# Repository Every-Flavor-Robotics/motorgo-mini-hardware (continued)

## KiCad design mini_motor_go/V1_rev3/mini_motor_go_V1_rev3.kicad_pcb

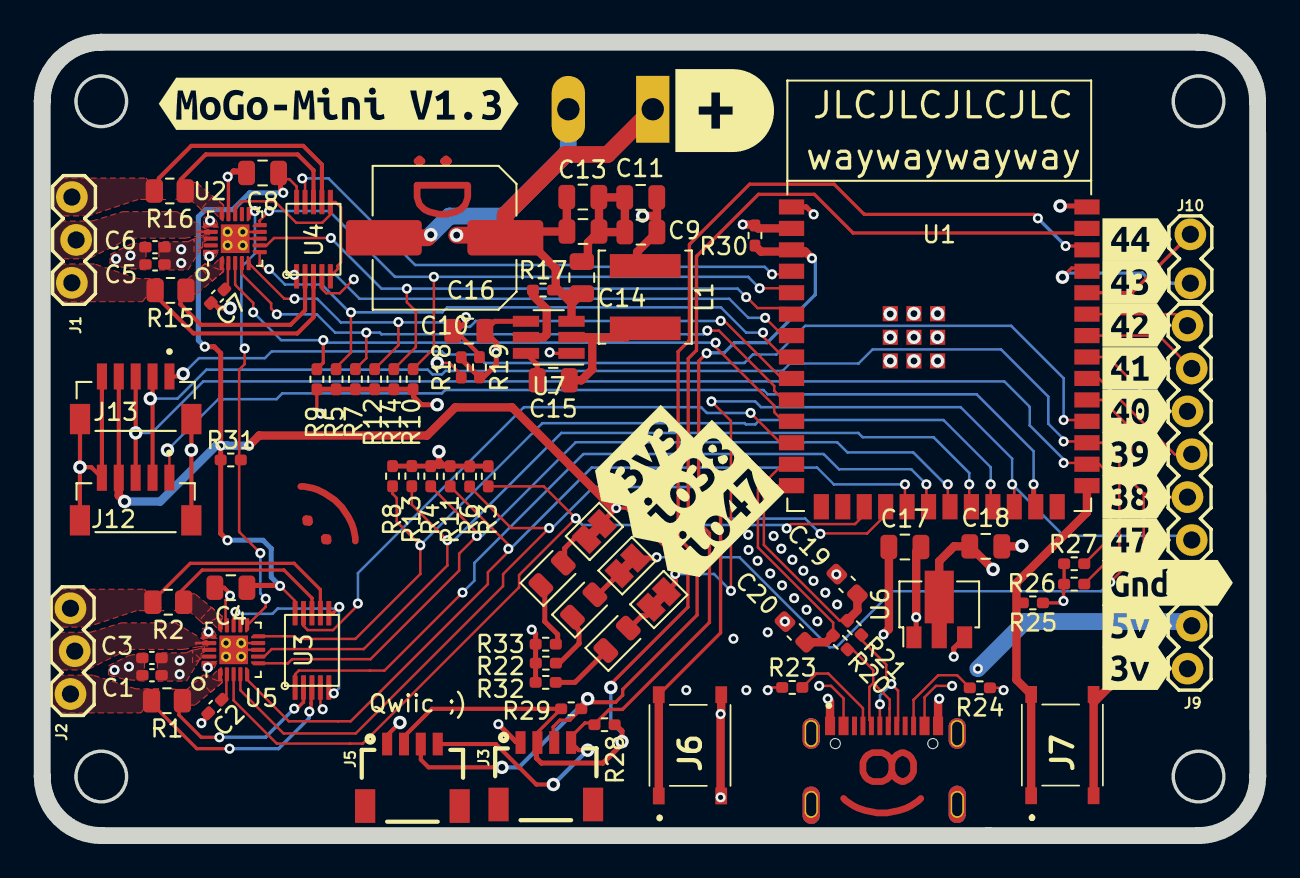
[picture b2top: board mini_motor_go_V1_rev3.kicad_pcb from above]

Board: 4 copper layers, 72.0 x 47.0 mm, 95 parts (0 on the bottom side), 68 nets.

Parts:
C1, C2, C3, C5, C6, C7: 10NF; C_0402_1005Metric_Pad0.74x0.62mm_HandSolder
C4, C8: 0.1UF; C_0805_2012Metric
C9, C11, C18: 22uF; C_0805_2012Metric
C10: 220uF; C_Elec_8x10.2
C12, C13, C17: 10uF; C_0805_2012Metric
C14, C15, C16: .1uF; C_0805_2012Metric
C19, C20: DNP; C_0603_1608Metric_Pad1.08x0.95mm_HandSolder
D1, D2, D3: LED; LED_0805_2012Metric
J1, J2: CONN_03POLAR_LOCK; 1X03_LOCK
J3, J5: I2C_STANDARDQWIIC; 1X04_1MM_RA
J6, J7: PTS526SM08SMTR2LFS
J8: TerminalBlock_Altech_AK300-2_P5.00mm
J9: Conn_01x09_Pin; 1X09_LOCK
J10: Conn_01x02_Pin; 1X02_LOCK
J11: USB4520-03-0-A_REVA; GCT_USB4520-03-0-A_REVA
J12, J13: BM05B-SRSS-TB_LF__SN_; JST_BM05B-SRSS-TB_LF__SN_
JP1, JP2, JP3: SolderJumper_2_Bridged; SolderJumper-2_P1.3mm_Bridged_Pad1.0x1.5mm
L1: SRP3212A-4R7M; L_Changjiang_FNR5020S
R1, R2, R15, R16: R_Shunt_US; R_0805_2012Metric
R3, R4, R5, R6, R7, R8, R9, R10, R11, R12, R13, R14: 1K; R_0402_1005Metric_Pad0.72x0.64mm_HandSolder
R17, R19: 54.9k; R_0402_1005Metric_Pad0.72x0.64mm_HandSolder
R18: 10k; R_0402_1005Metric_Pad0.72x0.64mm_HandSolder
R20, R21: 0; R_0402_1005Metric_Pad0.72x0.64mm_HandSolder
R22, R32, R33: 1k; R_0402_1005Metric_Pad0.72x0.64mm_HandSolder
R23, R24, R25, R26, R27, R28, R29, R30, R31: 5k1; R_0402_1005Metric_Pad0.72x0.64mm_HandSolder
U1: ESP32-S3-WROOM-1
U2, U5: TMC6300; TMC6300 3x3mm
U3, U4: INA2181; INA2181_VSSOP_10
U6: AZ1117C; SOT-89-3
U7: TPS562208; SOT-23-6_Handsoldering
kibuzzard-65733A0D: G***; kibuzzard-65733A0D
kibuzzard-65733A1B: G***; kibuzzard-65733A1B
kibuzzard-65733C02: G***; kibuzzard-65733C02
kibuzzard-65733C2B: G***; kibuzzard-65733C2B
kibuzzard-65733C3A: G***; kibuzzard-65733C3A
kibuzzard-65733C12: G***; kibuzzard-65733C12
kibuzzard-65733C20: G***; kibuzzard-65733C20
kibuzzard-65733C45: G***; kibuzzard-65733C45
kibuzzard-65733C60: G***; kibuzzard-65733C60
kibuzzard-65733C66: G***; kibuzzard-65733C66
kibuzzard-65733C85: G***; kibuzzard-65733C85
kibuzzard-65733FCF: G***; kibuzzard-65733FCF
kibuzzard-65733FF1: G***; kibuzzard-65733FF1
kibuzzard-66038D2F: G***; kibuzzard-66038D2F
kibuzzard-6573395A: G***; kibuzzard-6573395A
kibuzzard-65733965: G***; kibuzzard-65733965

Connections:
+3.3V: C4.1, C8.1, C18.1, J3.2 (VCC), J5.2 (VCC), J9.1, J12.4, J13.4, JP3.2 (B), R25.1, R26.1, R27.1, R28.1, R29.1, R30.1, R31.1, U1.2 (3V3), U3.10 (VS), U4.10 (VS), U6.2 (out)
+5V: C9.1, C11.1, C16.1, C17.1, J9.2, J11.A4_B9 (VBUS_A), J11.B4_A9 (VBUS_B), L1.1, R19.1, U6.3 (in)
+BATT: C1.1, C2.2, C3.2, C5.1, C6.2, C7.2, C10.1 (+), C12.2, C13.2, C14.2, J8.1 (+), R17.2, U2.18 (VS), U5.18 (VS), U7.3 (Vin)
/motor_controls/standby: R31.2, U2.11 (VIO/STDBY), U5.11 (VIO/STDBY)
GND: C1.2, C3.1, C4.2, C5.2, C6.1, C8.2, C10.2 (-), C17.2, C18.2, C19.2, C20.2, J3.1 (GND), J5.1 (GND), J6.3, J6.4, J7.3, J7.4, J8.2 (-), J9.3, J11.A1_B12 (GND_A), J11.B1_A12 (GND_B), J12.5, J12.S1 (SHIELD), J12.S2 (SHIELD__1), J13.5, J13.S1 (SHIELD), J13.S2 (SHIELD__1), R3.1, R4.1, R5.1, R6.1, R7.1, R8.1, R9.1, R10.1, R11.1, R12.1, R13.1, R14.1, R18.1, R22.2, R23.1, R24.1, R32.2, R33.2, U1.1 (GND), U1.40 (GND), U1.41 (GND), U2.8 (GND), U2.9 (GND), U2.14 (GND), U2.16 (BRUV), U2.20 (BRW), U2.21 (PAD), U3.4 (GND), U4.4 (GND), U5.8 (GND), U5.9 (GND), U5.14 (GND), U5.16 (BRUV), U5.20 (BRW), U5.21 (PAD), U6.1 (adj), U7.1 (GND)
unnamed: C9.2, C11.2, C12.1, C13.1, C14.1
unnamed: D1.2 (A), JP1.1 (A)
unnamed: D1.1 (K), R32.1
unnamed: D2.2 (A), JP2.1 (A)
unnamed: D2.1 (K), R22.1
unnamed: D3.2 (A), JP3.1 (A)
unnamed: D3.1 (K), R33.1
unnamed: J9.6, U1.32 (MTCK/GPIO39/CLK_OUT3/SUBSPICS1)
unnamed: J9.7, U1.33 (MTDO/GPIO40/CLK_OUT2)
unnamed: J9.8, U1.34 (MTDI/GPIO41/CLK_OUT1)
unnamed: J9.9, U1.35 (MTMS/GPIO42)
unnamed: J10.1, U1.37 (U0TXD/GPIO43/CLK_OUT1)
unnamed: J10.2, U1.36 (U0RXD/GPIO44/CLK_OUT2)
unnamed: J11.A5 (CC1), R23.2
unnamed: J11.B5 (CC2), R24.2
unnamed: J11.A7 (DN1), J11.B7 (DN2), R20.2
unnamed: J11.A6 (DP1), J11.B6 (DP2), R21.2
unnamed: J6.1, J6.2, R30.2, U1.3 (EN)
unnamed: J7.1, J7.2, R25.2, U1.27 (GPIO0/BOOT)
unnamed: U2.13 (1.8v_out), U4.5 (ref_1), U4.6 (ref_2)
unnamed: R16.1, U2.15 (U), U4.8 (in-2)
unnamed: J1.2, U2.17 (V)
unnamed: C7.1, U2.2 (VCP)
unnamed: R15.1, U2.1 (W), U4.2 (in-1)
unnamed: J2.1, R1.2, U3.3 (in+1)
unnamed: J2.3, R2.2, U3.7 (in+2)
unnamed: R1.1, U3.2 (in-1), U5.1 (W)
unnamed: R2.1, U3.8 (in-2), U5.15 (U)
unnamed: U3.5 (ref_1), U3.6 (ref_2), U5.13 (1.8v_out)
unnamed: J1.1, R15.2, U4.3 (in+1)
unnamed: J1.3, R16.2, U4.7 (in+2)
unnamed: J2.2, U5.17 (V)
unnamed: C2.1, U5.2 (VCP)
unnamed: R17.1, U7.5 (EN)
unnamed: C15.1, L1.2, U7.2 (SW)
unnamed: C15.2, U7.6 (VBST)
unnamed: C16.2, R18.2, R19.2, U7.4 (VFB)
enc_scl: J12.2, J13.2, R26.2, U1.29 (SPIIO7/GPIO36/FSPICLK/SUBSPICLK)
enc_sda: J12.3, J13.3, R27.2, U1.28 (SPIIO6/GPIO35/FSPID/SUBSPID)
gpio38: J9.5, JP2.2 (B), U1.31 (GPIO38/FSPIWP/SUBSPIWP)
gpio47: J9.4, U1.24 (GPIO47/SPICLK_P/SUBSPICLK_P_DIFF)
m1_current_sense_u: U1.7 (GPIO7/TOUCH7/ADC1_CH6), U4.1 (out_1)
m1_current_sense_w: U1.4 (GPIO4/TOUCH4/ADC1_CH3), U4.9 (out_2)
m1_enc_cs: J13.1, U1.30 (SPIDQS/GPIO37/FSPIQ/SUBSPIQ)
m1_uh: R9.2, U1.11 (GPIO18/U1RXD/ADC2_CH7/CLK_OUT3), U2.3 (UH)
m1_ul: R5.2, U1.8 (GPIO15/U0RTS/ADC2_CH4/XTAL_32K_P), U2.6 (UL)
m1_vh: R7.2, U1.10 (GPIO17/U1TXD/ADC2_CH6), U2.4 (VH)
m1_vl: R10.2, U1.5 (GPIO5/TOUCH5/ADC1_CH4), U2.10 (VL)
m1_wh: R12.2, U1.9 (GPIO16/U0CTS/ADC2_CH5/XTAL_32K_N), U2.5 (WH)
m1_wl: R14.2, U1.6 (GPIO6/TOUCH6/ADC1_CH5), U2.7 (WL)
m2_current_sense_u: U1.12 (GPIO8/TOUCH8/ADC1_CH7/SUBSPICS1), U3.9 (out_2)
m2_current_sense_w: U1.20 (GPIO12/TOUCH12/ADC2_CH1/FSPICLK/FSPIIO6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), U3.1 (out_1)
m2_enc_cs: J12.1, U1.25 (GPIO48/SPICLK_N/SUBSPICLK_N_DIFF)
m2_uh: R3.2, U1.17 (GPIO9/TOUCH9/ADC1_CH8/FSPIHD/SUBSPIHD), U5.3 (UH)
m2_ul: R4.2, U1.21 (GPIO13/TOUCH13/ADC2_CH2/FSPIQ/FSPIIO7/S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), U5.6 (UL)
m2_vh: R6.2, U1.18 (GPIO10/TOUCH10/ADC1_CH9/FSPICS0/FSPIIO4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), U5.4 (VH)
m2_vl: R8.2, U1.23 (GPIO21), U5.10 (VL)
m2_wh: R11.2, U1.19 (GPIO11/TOUCH11/ADC2_CH0/FSPID/FSPIIO5/S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), U5.5 (WH)
m2_wl: R13.2, U1.22 (GPIO14/TOUCH14/ADC2_CH3/FSPIWP/FSPIDQS/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), U5.7 (WL)
scl: J3.4 (SCL), J5.4 (SCL), R28.2, U1.39 (GPIO1/TOUCH1/ADC1_CH0)
sda: J3.3 (SDA), J5.3 (SDA), R29.2, U1.38 (GPIO2/TOUCH2/ADC1_CH1)
usb_d+: C19.1, R21.1, U1.14 (GPIO20/U1CTS/ADC2_CH9/CLK_OUT1/USB_D+)
usb_d-: C20.1, R20.1, U1.13 (GPIO19/U1RTS/ADC2_CH8/CLK_OUT2/USB_D-)

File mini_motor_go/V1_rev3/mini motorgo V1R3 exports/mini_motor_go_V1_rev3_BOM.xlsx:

Manufacturer Part Number | Qty | Designator | Customer Supply | Customer Remark | Value | Footprint | Datasheet |  | LCSC Part Number | Manufacturer_Name |  | note
CC0402KRX7R9BB103 | 6 | C1-C3, C5-C7 | N |  | 10NF | Capacitor_SMD:C_0402_1005Metric_Pad0.74x0.62mm_HandSolder | https://www.lcsc.com/product-detail/Multilayer-Ceramic-Capac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 |  | C60133 | YAGEO |  | footprint match
08055C104KAZ2A | 2 | C4, C8 | N |  | 0.1UF | Capacitor_SMD:C_0805_2012Metric | https://www.lcsc.com/product-detail/Multilayer-Ceramic-Capac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 |  | C6641151 | Kyocera AVX |  | footprint match
CL21A226MAYNNNE | 3 | C9, C11, C18 | N |  | 22uF | Capacitor_SMD:C_0805_2012Metric | https://www.lcsc.com/product-detail/Multilayer-Ceramic-Capac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 |  | C602037 | SAMSUNG |  | footprint match
VT1E221M0810 | 1 | C10 | N |  | 220uF | Capacitor_SMD:C_Elec_8x10.2 | https://www.lcsc.com/product-detail/Aluminum-Electrolytic-Ca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 |  | C191825 | ROQANG |  | footprint match
CL21A106KOQNNNE | 3 | C12, C13, C17 | N |  | 10uF | Capacitor_SMD:C_0805_2012Metric | https://www.lcsc.com/product-detail/Multilayer-Ceramic-Capac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 |  | C1713 | SAMSUNG |  | footprint match
08055C104KAZ2A | 3 | C14-C16 | N |  | .1uF | Capacitor_SMD:C_0805_2012Metric | https://www.lcsc.com/product-detail/Multilayer-Ceramic-Capac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 |  | C6641151 | Kyocera AVX |  | footprint match
XL-2012SURC | 1 | D1 | N |  | LED | LED_SMD:LED_0805_2012Metric | https://www.lcsc.com/product-detail/Light-Emitting-Diodes-LE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 |  | C965812 | XINGLIGHT |  | red - footprint match
XL-2012UYC | 1 | D2 | N |  | LED | LED_SMD:LED_0805_2012Metric | https://www.lcsc.com/product-detail/Light-Emitting-Diodes-LE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 |  | C965814 | XINGLIGHT |  | yellow - footprint match
XL-2012UGC | 1 | D3 | N |  | LED | LED_SMD:LED_0805_2012Metric | https://www.lcsc.com/product-detail/Light-Emitting-Diodes-LE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 |  | C965815 | XINGLIGHT |  | green - footprint match
DNP | 2 | J1, J2 | DNP |  | CONN_03POLAR_LOCK | aa_sparkfun_connectors:1X03_LOCK |  |  | DNP | DNP |  | DNP
SM04B-SRSS-TB(LF)(SN) | 2 | J3, J5 | N |  | I2C_STANDARDQWIIC | aa_sparkfun_connectors:1X04_1MM_RA | https://www.lcsc.com/product-detail/Wire-To-Board-Wire-To-Wi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 |  | C160404 | JST |  | footprint discrepancy
PTS526SK15SMTR2LFS | 2 | J6, J7 | N |  | ~ | aaa_SamacSys_Parts:PTS526SM08SMTR2LFS | https://www.lcsc.com/product-detail/Tactile-Switches_C-K-PTS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 |  | C2689521 | C&K |  | footprint match
WJ126V-5.0-2P | 1 | J8 | N |  | ~ | aaa_motorgo_components:xt30 | https://www.lcsc.com/product-detail/Screw-terminal_Ningbo-Ka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 |  | C8404 | Ningbo Kangnex Elec |  | footprint discrepancy
DNP | 1 | J9 | DNP |  | Conn_01x09_Pin | aa_sparkfun_connectors:1X09_LOCK |  |  | DNP | DNP |  | DNP
DNP | 1 | J10 | DNP |  | Conn_01x02_Pin | aa_sparkfun_connectors:1X02_LOCK |  |  | DNP | DNP |  | DNP
TYPE-C16P3MDDGP073 | 1 | J11 | N |  | USB4520-03-0-A_REVA | aaa_motorgo_components:GCT_USB4520-03-0-A_REVA | https://www.lcsc.com/product-detail/USB-Connectors_SHOU-HAN-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 |  | C2965608 | SHOU HAN |  | footprint match
SM05B-NSHSS-TB(LF)(SN) | 2 | J12, J13 | N |  | BM05B-SRSS-TB_LF__SN_ | SnapEDA Library:JST_BM05B-SRSS-TB_LF__SN_ | https://www.lcsc.com/product-detail/Wire-To-Board-Wire-To-Wi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 |  | C268096 | JST |  | footprint match
DNP | 3 | JP1-JP3 | DNP |  | SolderJumper_2_Bridged | Jumper:SolderJumper-2_P1.3mm_Bridged_Pad1.0x1.5mm |  |  | DNP | DNP |  | DNP
FNR5020S4R7MT | 1 | L1 | N |  | SRP3212A-4R7M | aaa_SamacSys_Parts:INDC3225X120N | https://www.lcsc.com/product-detail/Power-Inductors_cjiang-C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 |  | C167930 | CJIANG |  | footprint match
RM2512FBR001GS | 4 | R1, R2, R15, R16 | N |  | R_Shunt_US | aaa_SamacSys_Parts:RESC1608X55N | https://www.lcsc.com/product-detail/Current-Sense-Resistors-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 |  | C5154734 | LIZ Elec |  | footprint match
SCR0402F1K | 12 | R3-R14 | N |  | 1K | Resistor_SMD:R_0402_1005Metric_Pad0.72x0.64mm_HandSolder | https://www.lcsc.com/product-detail/Chip-span-style-backgrou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 |  | C3015791 | VO |  | footprint match
WR04X5492FTL | 2 | R17, R19 | N |  | 54.9k | Resistor_SMD:R_0402_1005Metric_Pad0.72x0.64mm_HandSolder | https://www.lcsc.com/product-detail/Chip-span-style-backgrou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 |  | C170335 | Walsin Tech Corp |  | footprint match
SCR0402F10K | 1 | R18 | N |  | 10k | Resistor_SMD:R_0402_1005Metric_Pad0.72x0.64mm_HandSolder | https://www.lcsc.com/product-detail/Chip-span-style-backgrou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 |  | C3015825 | VO |  | footprint match
FRC0402F0000TS | 2 | R20, R21 | N |  | 0 | Resistor_SMD:R_0402_1005Metric_Pad0.72x0.64mm_HandSolder | https://www.lcsc.com/product-detail/Chip-span-style-backgrou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 |  | C2906858 | FOJAN |  | footprint match
SCR0402F1K | 3 | R22, R32, R33 | N |  | 1k | Resistor_SMD:R_0402_1005Metric_Pad0.72x0.64mm_HandSolder | https://www.lcsc.com/product-detail/Chip-span-style-backgrou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 |  | C3015791 | VO |  | footprint match
CR0402FF5101G | 9 | R23-R31 | N |  | 5k1 | Resistor_SMD:R_0402_1005Metric_Pad0.72x0.64mm_HandSolder | https://www.lcsc.com/product-detail/Chip-span-style-backgrou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 |  | C100461 | LIZ Elec |  | footprint match
ESP32-S3-WROOM-1-N8 | 1 | U1 | N |  | ESP32-S3-WROOM-1 | aaa_espressif_github:ESP32-S3-WROOM-1 | https://www.lcsc.com/product-detail/WiFi-Modules_Espressif-S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 |  | C2913198 | Espressif Systems |  | footprint discrepancy
TMC6300-LA-T | 2 | U2, U5 | N |  | TMC6300 | aaa_trinamic:TMC6300 3x3mm | https://www.mouser.com/ProductDetail/ADI-Trinamic/TMC6300-LA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 |  | n/a | ADI Trinamic |  | footprint discrepancy
INA2181A4QDGSRQ1 | 2 | U3, U4 | N |  | INA2181 | aaa_motorgo_components:INA2181_VSSOP_10 | https://www.lcsc.com/product-detail/Current-Sensing-Amplifie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 |  | C2058024 | Texas Instruments |  | footprint discrepancy
AZ1117CR-3.3TRG1 | 1 | U6 | N |  | AZ1117C | Package_TO_SOT_SMD:SOT-89-3 | https://www.lcsc.com/product-detail/Linear-Voltage-Regulator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 |  | C460428 | Diodes Incorporated |  | footprint match
TPS562208DDCR | 1 | U7 | N |  | TPS562208 | Package_TO_SOT_SMD:SOT-23-6_Handsoldering | https://www.lcsc.com/product-detail/DC-DC-Converters_Texas-I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 |  | C91301 | Texas Instruments |  | footprint match

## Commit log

2023-12-05 first commit big unfiltered dump
2023-12-05 adding v1.3 files to repo
2023-12-07 slight update to part selection table
2023-12-07 rev3 changes
2023-12-07 restructure and add .gitIgnore
2023-12-07 added part numbers and links to most parts. Ready for review. -TS
2023-12-07 made 2 minor p/n changes
2023-12-08 reviewed value table in schematics, updated footprints on board minor improvements
2023-12-08 reverted some bad merge artifacts to working version
2023-12-08 try to resolve differences between teams
2023-12-08 changed .1uf caps to 0805 C14-C16
2023-12-08 updated part numbers for final review, compared eschema footprints to pcb file. see notes in eschema part list. TS
2023-12-09 added gerber, centroid, and bom exports for quotes
2023-12-14 updating CAD exports. TS
2023-12-14 revision meeting with tom edits
2023-12-15 generated new design files after final engineering review. TS
2024-02-06 Update README.md picture
2024-03-27 fix indicator led silkscreen io8 to io47
2024-03-27 replace exports folder with newly generated ones since silkscreen fix
2024-03-27 deleted and renamed all files
2025-07-21 failed to make atopile project success
2025-07-28 initial revision kicad pre-layout
2025-07-28 remove unused file name
2025-07-28 update motor controls schema
2025-07-29 incremental layout progress
2025-07-31 Ready for ordering pcb files
2025-07-31 remove blender assets, unused
2025-07-31 added obsidian workspace file
